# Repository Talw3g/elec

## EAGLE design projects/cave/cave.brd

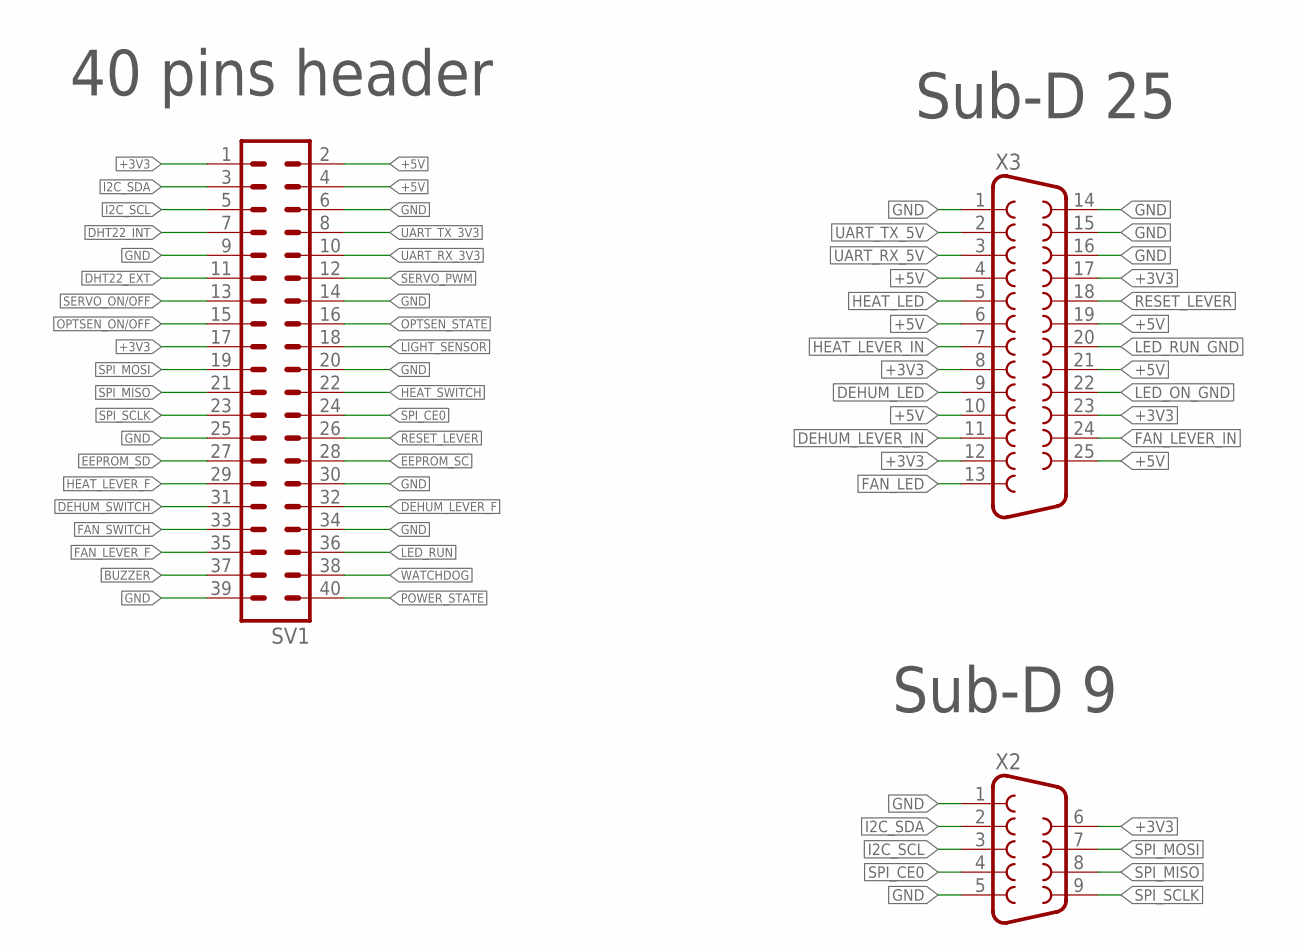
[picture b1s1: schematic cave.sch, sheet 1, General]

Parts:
SV1: MA20-2
X2: F09V
X3: F25V

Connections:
+3V3: SV1.1, SV1.17, X2.6, X3.8, X3.12, X3.17, X3.23; also elsewhere on the board
+5V: SV1.2, SV1.4, X3.4, X3.6, X3.10, X3.19, X3.21, X3.25; also elsewhere on the board
BUZZER: SV1.37; also elsewhere on the board
DEHUM_LED: X3.9; also elsewhere on the board
DEHUM_LEVER_F: SV1.32; also elsewhere on the board
DEHUM_LEVER_IN: X3.11; also elsewhere on the board
DEHUM_SWITCH: SV1.31; also elsewhere on the board
DHT22_EXT: SV1.11; also elsewhere on the board
DHT22_INT: SV1.7; also elsewhere on the board
EEPROM_SC: SV1.28
EEPROM_SD: SV1.27
FAN_LED: X3.13; also elsewhere on the board
FAN_LEVER_F: SV1.35; also elsewhere on the board
FAN_LEVER_IN: X3.24; also elsewhere on the board
FAN_SWITCH: SV1.33; also elsewhere on the board
GND: SV1.6, SV1.9, SV1.14, SV1.20, SV1.25, SV1.30, SV1.34, SV1.39, X2.1, X2.5, X3.1, X3.14, X3.15, X3.16; also elsewhere on the board
HEAT_LED: X3.5; also elsewhere on the board
HEAT_LEVER_F: SV1.29; also elsewhere on the board
HEAT_LEVER_IN: X3.7; also elsewhere on the board
HEAT_SWITCH: SV1.22; also elsewhere on the board
I2C_SCL: SV1.5, X2.3
I2C_SDA: SV1.3, X2.2
LED_ON_GND: X3.22; also elsewhere on the board
LED_RUN: SV1.36; also elsewhere on the board
LED_RUN_GND: X3.20; also elsewhere on the board
LIGHT_SENSOR: SV1.18; also elsewhere on the board
OPTSEN_ON/OFF: SV1.15; also elsewhere on the board
OPTSEN_STATE: SV1.16; also elsewhere on the board
POWER_STATE: SV1.40; also elsewhere on the board
RESET_LEVER: SV1.26, X3.18; also elsewhere on the board
SERVO_ON/OFF: SV1.13; also elsewhere on the board
SERVO_PWM: SV1.12; also elsewhere on the board
SPI_CE0: SV1.24, X2.4
SPI_MISO: SV1.21, X2.8
SPI_MOSI: SV1.19, X2.7
SPI_SCLK: SV1.23, X2.9
UART_RX_3V3: SV1.10; also elsewhere on the board
UART_RX_5V: X3.3; also elsewhere on the board
UART_TX_3V3: SV1.8; also elsewhere on the board
UART_TX_5V: X3.2; also elsewhere on the board
WATCHDOG: SV1.38; also elsewhere on the board

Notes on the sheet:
40 pins header
Sub-D 25
Sub-D 9

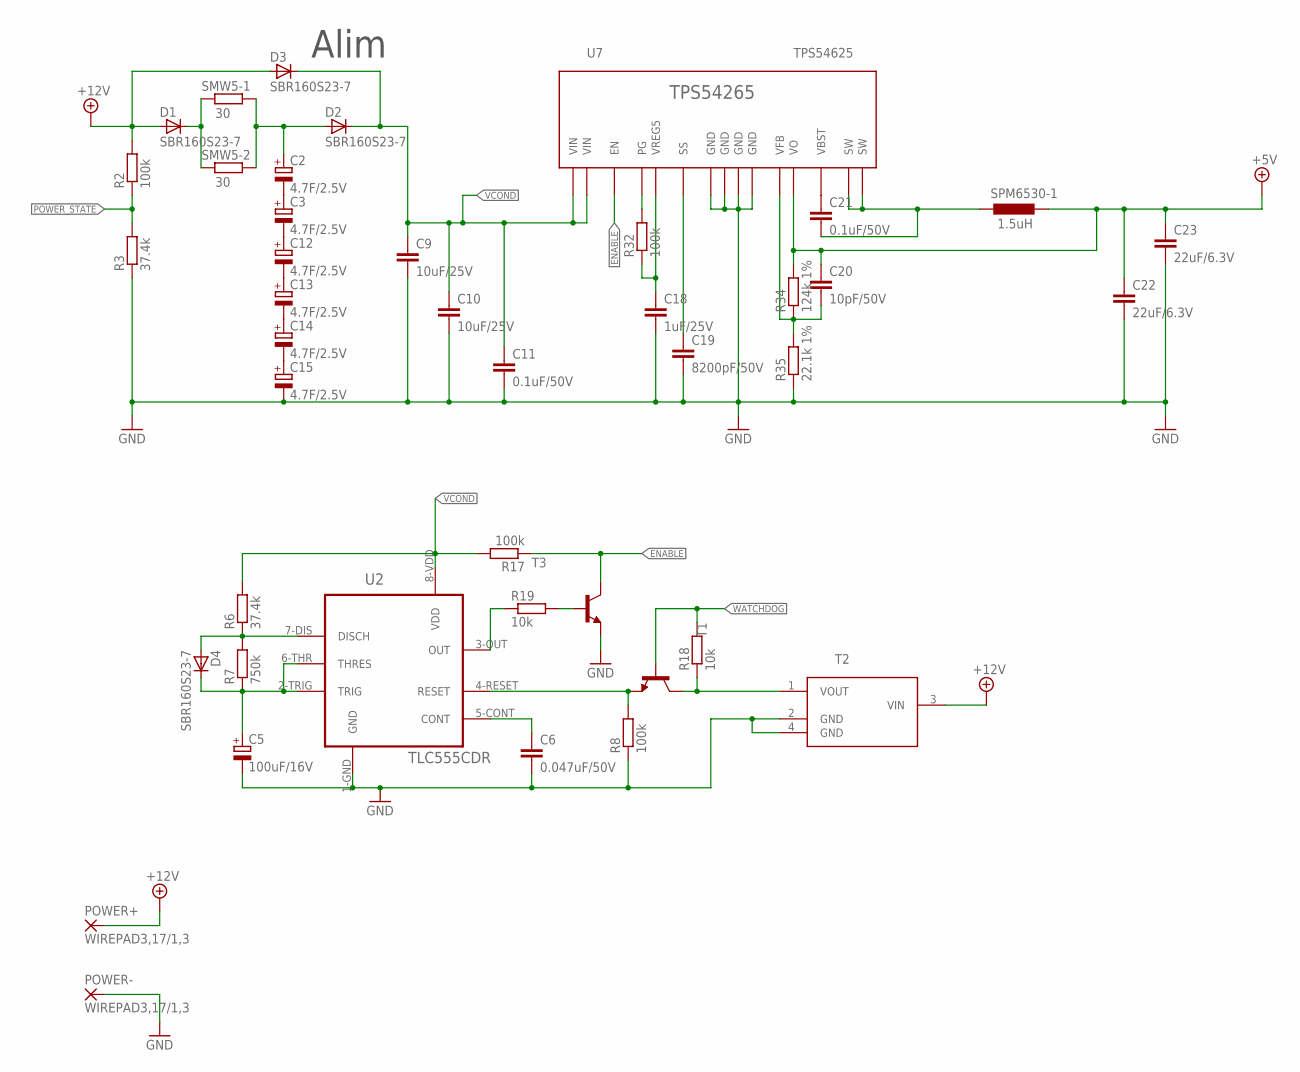
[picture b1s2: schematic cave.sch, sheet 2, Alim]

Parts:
C2, C3, C12, C13, C14, C15: 4.7F/2.5V; E5-10,5
C5: 100uF/16V; D/7343-31W
C6: 0.047uF/50V; C0603
C9, C10: 10uF/25V; C0805
C11, C21: 0.1uF/50V; C0603
C18: 1uF/25V; C0603
C19: 8200pF/50V; C0603
C20: 10pF/50V; C0603
C22, C23: 22uF/6.3V; C0805
D1, D2, D3, D4: SBR160S23-7; SOT23
POWER+: WIREPAD3,17/1,3; 3,17/1,3
POWER-: WIREPAD3,17/1,3; 3,17/1,3
R2, R8, R17, R32: 100k; R0603
R3, R6: 37.4k; R0603
R7: 750k; R0603
R18, R19: 10k; R0603
R34: 124k 1%; R0603
R35: 22.1k 1%; R0603
SMW5-1, SMW5-2: 30; SM_5
SPM6530-1: 1.5uH; 6530
T1, T3: MMBT2369LT1-NPN-SOT23-BEC; SOT23-BEC
T2: L78L33ACUTR; SOT150P400X160-4N
U2: TLC555CDR; SOIC127P600X175-8N
U7: TPS54625; HTSSOP-14

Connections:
+5V: C20.1, C22.1, C23.1, R34.2, SPM6530-1.P$2, U7.P$1 (VO); also elsewhere on the board
+12V: D1.1 (A), D3.1 (A), POWER+.1, R2.2, T2.3 (VIN); also elsewhere on the board
ENABLE: R17.1, T3.C, U7.P$7 (EN)
GND: C5.-, C6.2, C9.2, C10.2, C11.2, C15.-, C18.2, C19.2, C22.2, C23.2, POWER-.1, R3.1, R8.1, R35.1, T2.2 (GND), T2.4 (GND), T3.E, U2.1-GND (GND), U7.P$5 (GND), U7.P$8 (GND), U7.P$9 (GND), U7.P$15 (GND); also elsewhere on the board
unnamed: C2.+, D2.1 (A), SMW5-1.P$2 (2), SMW5-2.P$2 (2)
unnamed: C2.-, C3.+
unnamed: C3.-, C12.+
unnamed: D1.3 (C), SMW5-1.P$1 (1), SMW5-2.P$1 (1)
unnamed: D4.1 (A), R6.1, R7.2, U2.7-DIS (DISCH)
unnamed: C5.+, D4.3 (C), R7.1, U2.2-TRIG (TRIG), U2.6-THR (THRES)
unnamed: C12.-, C13.+
unnamed: C6.1, U2.5-CONT (CONT)
unnamed: R18.1, T1.C, T2.1 (VOUT)
unnamed: R8.2, T1.E, U2.4-RESET (RESET)
unnamed: R19.1, U2.3-OUT (OUT)
unnamed: R19.2, T3.B
unnamed: C13.-, C14.+
unnamed: C14.-, C15.+
unnamed: C18.1, R32.1, U7.P$3 (VREG5)
unnamed: R32.2, U7.P$6 (PG)
unnamed: C19.1, U7.P$4 (SS)
unnamed: C20.2, R34.1, R35.2, U7.P$2 (VFB)
unnamed: C21.1, U7.P$12 (VBST)
unnamed: C21.2, SPM6530-1.P$1, U7.P$10 (SW), U7.P$11 (SW)
POWER_STATE: R2.1, R3.2; also elsewhere on the board
VCOND: C9.1, C10.1, C11.1, D2.3 (C), D3.3 (C), R6.2, R17.2, U2.8-VDD (VDD), U7.P$13 (VIN), U7.P$14 (VIN)
WATCHDOG: R18.2, T1.B; also elsewhere on the board

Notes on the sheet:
Alim

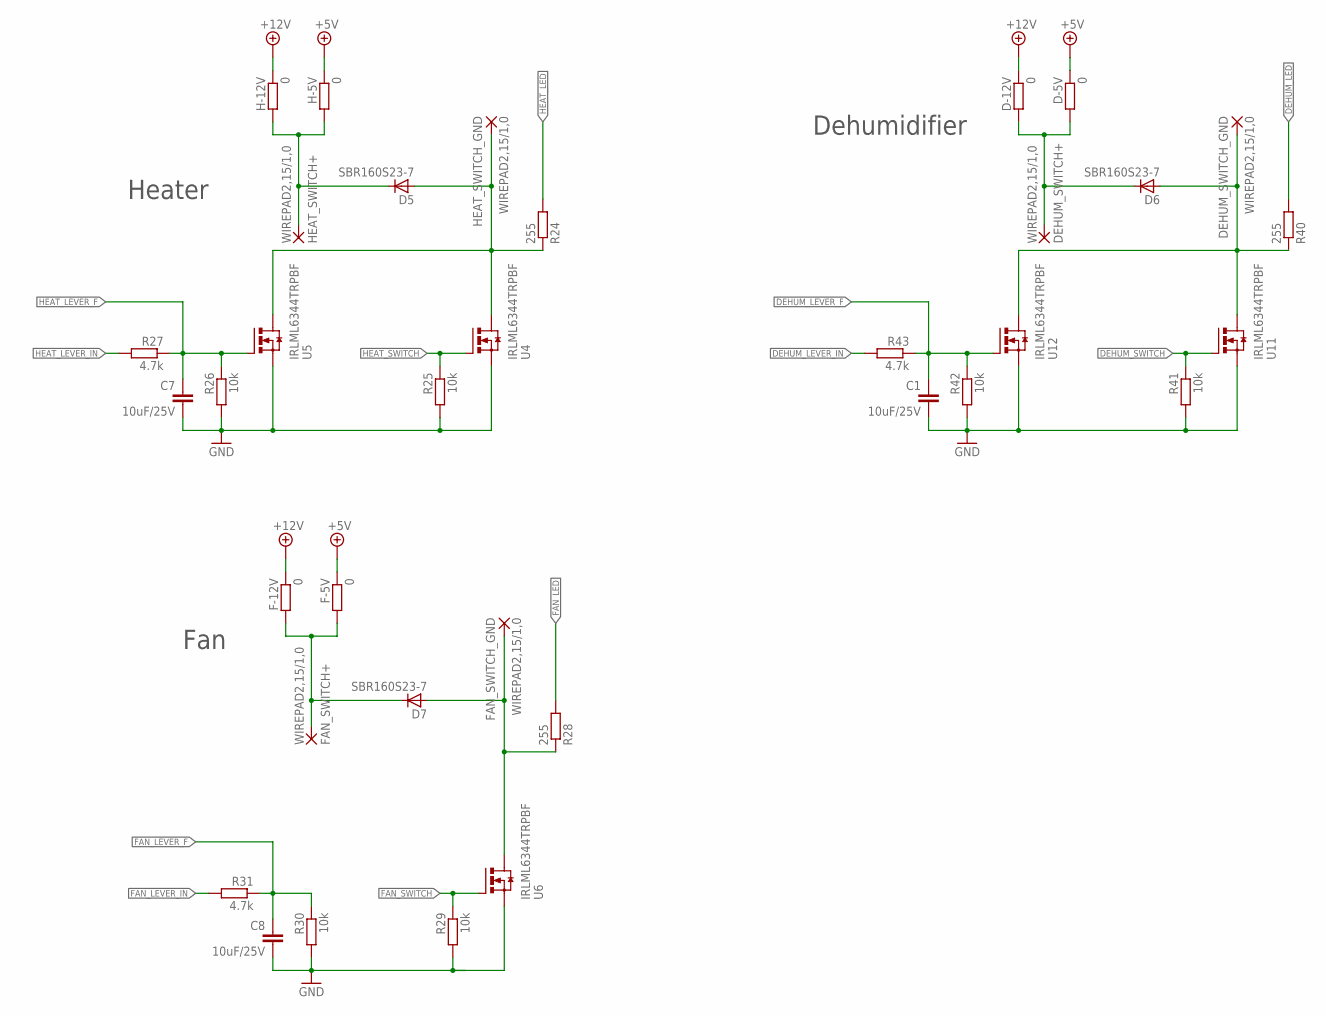
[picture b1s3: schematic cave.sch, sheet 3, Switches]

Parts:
C1, C7, C8: 10uF/25V; C0805
D5, D6, D7: SBR160S23-7; SOT23
D-5V, D-12V: 0; R0805
DEHUM_SWITCH+: WIREPAD2,15/1,0; 2,15/1,0
DEHUM_SWITCH_GND: WIREPAD2,15/1,0; 2,15/1,0
F-5V, F-12V: 0; R0805
FAN_SWITCH+: WIREPAD2,15/1,0; 2,15/1,0
FAN_SWITCH_GND: WIREPAD2,15/1,0; 2,15/1,0
H-5V, H-12V: 0; R0805
HEAT_SWITCH+: WIREPAD2,15/1,0; 2,15/1,0
HEAT_SWITCH_GND: WIREPAD2,15/1,0; 2,15/1,0
R24, R28, R40: 255; R0805
R25, R26, R29, R30, R41, R42: 10k; R0603
R27, R31, R43: 4.7k; R0603
U4, U5, U6, U11, U12: IRLML6344TRPBF; SOT95P240X112-3N

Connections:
+5V: D-5V.1, F-5V.1, H-5V.1; also elsewhere on the board
+12V: D-12V.1, F-12V.1, H-12V.1; also elsewhere on the board
DEHUM_GND: D6.1 (A), DEHUM_SWITCH_GND.1, R40.1, U11.3 (D), U12.3 (D)
DEHUM_LED: R40.2; also elsewhere on the board
DEHUM_LEVER_F: C1.1, R42.1, R43.1, U12.1 (G); also elsewhere on the board
DEHUM_LEVER_IN: R43.2; also elsewhere on the board
DEHUM_SWITCH: R41.1, U11.1 (G); also elsewhere on the board
FAN_GND: D7.1 (A), FAN_SWITCH_GND.1, R28.1, U6.3 (D)
FAN_LED: R28.2; also elsewhere on the board
FAN_LEVER_F: C8.1, R30.1, R31.1; also elsewhere on the board
FAN_LEVER_IN: R31.2; also elsewhere on the board
FAN_SWITCH: R29.1, U6.1 (G); also elsewhere on the board
GND: C1.2, C7.2, C8.2, R25.2, R26.2, R29.2, R30.2, R41.2, R42.2, U4.2 (S), U5.2 (S), U6.2 (S), U11.2 (S), U12.2 (S); also elsewhere on the board
HEAT_GND: D5.1 (A), HEAT_SWITCH_GND.1, R24.1, U4.3 (D), U5.3 (D)
HEAT_LED: R24.2; also elsewhere on the board
HEAT_LEVER_F: C7.1, R26.1, R27.1, U5.1 (G); also elsewhere on the board
HEAT_LEVER_IN: R27.2; also elsewhere on the board
HEAT_SWITCH: R25.1, U4.1 (G); also elsewhere on the board
unnamed: D7.3 (C), F-5V.2, F-12V.2, FAN_SWITCH+.1
unnamed: D5.3 (C), H-5V.2, H-12V.2, HEAT_SWITCH+.1
unnamed: D6.3 (C), D-5V.2, D-12V.2, DEHUM_SWITCH+.1

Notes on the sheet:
Heater
Dehumidifier
Fan

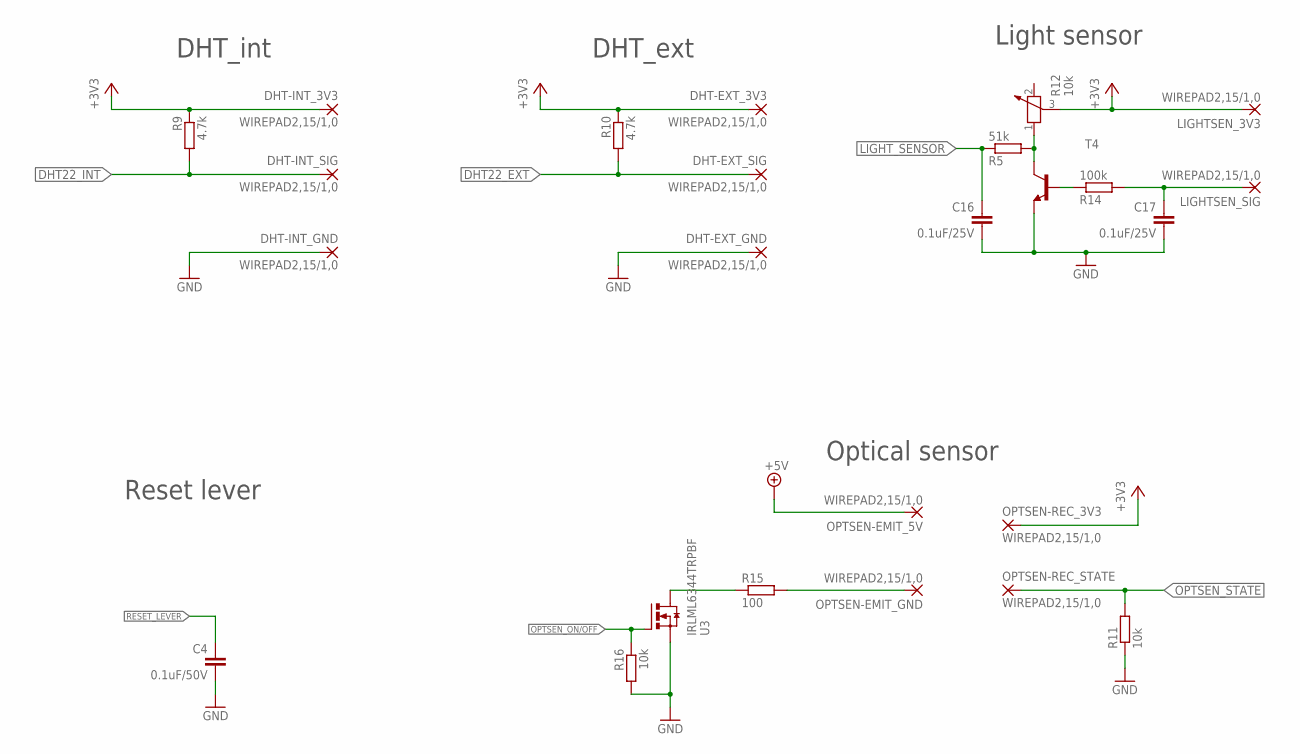
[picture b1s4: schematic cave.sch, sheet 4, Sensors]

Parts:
C4: 0.1uF/50V; C0603
C16, C17: 0.1uF/25V; C0603
DHT-EXT_3V3: WIREPAD2,15/1,0; 2,15/1,0
DHT-EXT_GND: WIREPAD2,15/1,0; 2,15/1,0
DHT-EXT_SIG: WIREPAD2,15/1,0; 2,15/1,0
DHT-INT_3V3: WIREPAD2,15/1,0; 2,15/1,0
DHT-INT_GND: WIREPAD2,15/1,0; 2,15/1,0
DHT-INT_SIG: WIREPAD2,15/1,0; 2,15/1,0
LIGHTSEN_3V3: WIREPAD2,15/1,0; 2,15/1,0
LIGHTSEN_SIG: WIREPAD2,15/1,0; 2,15/1,0
OPTSEN-EMIT_5V: WIREPAD2,15/1,0; 2,15/1,0
OPTSEN-EMIT_GND: WIREPAD2,15/1,0; 2,15/1,0
OPTSEN-REC_3V3: WIREPAD2,15/1,0; 2,15/1,0
OPTSEN-REC_STATE: WIREPAD2,15/1,0; 2,15/1,0
R5: 51k; R0603
R9, R10: 4.7k; R0603
R11, R16: 10k; R0603
R12: 10k; PT-SPIN
R14: 100k; R0603
R15: 100; R0805
T4: MMBT2369LT1-NPN-SOT23-BEC; SOT23-BEC
U3: IRLML6344TRPBF; SOT95P240X112-3N

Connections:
+3V3: DHT-EXT_3V3.1, DHT-INT_3V3.1, LIGHTSEN_3V3.1, OPTSEN-REC_3V3.1, R9.1, R10.1, R12.3; also elsewhere on the board
+5V: OPTSEN-EMIT_5V.1; also elsewhere on the board
DHT22_EXT: DHT-EXT_SIG.1, R10.2; also elsewhere on the board
DHT22_INT: DHT-INT_SIG.1, R9.2; also elsewhere on the board
GND: C4.2, C16.2, C17.2, DHT-EXT_GND.1, DHT-INT_GND.1, R11.1, R16.2, T4.E, U3.2 (S); also elsewhere on the board
LIGHT_SENSOR: C16.1, R5.1; also elsewhere on the board
LIGHT_SENSOR_UNFILTERED: R5.2, R12.1, T4.C
unnamed: OPTSEN-EMIT_GND.1, R15.2
unnamed: R15.1, U3.3 (D)
unnamed: R14.1, T4.B
unnamed: C17.1, LIGHTSEN_SIG.1, R14.2
OPTSEN_ON/OFF: R16.1, U3.1 (G); also elsewhere on the board
OPTSEN_STATE: OPTSEN-REC_STATE.1, R11.2; also elsewhere on the board
RESET_LEVER: C4.1; also elsewhere on the board

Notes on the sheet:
DHT_int
DHT_ext
Optical sensor
Light sensor
Reset lever

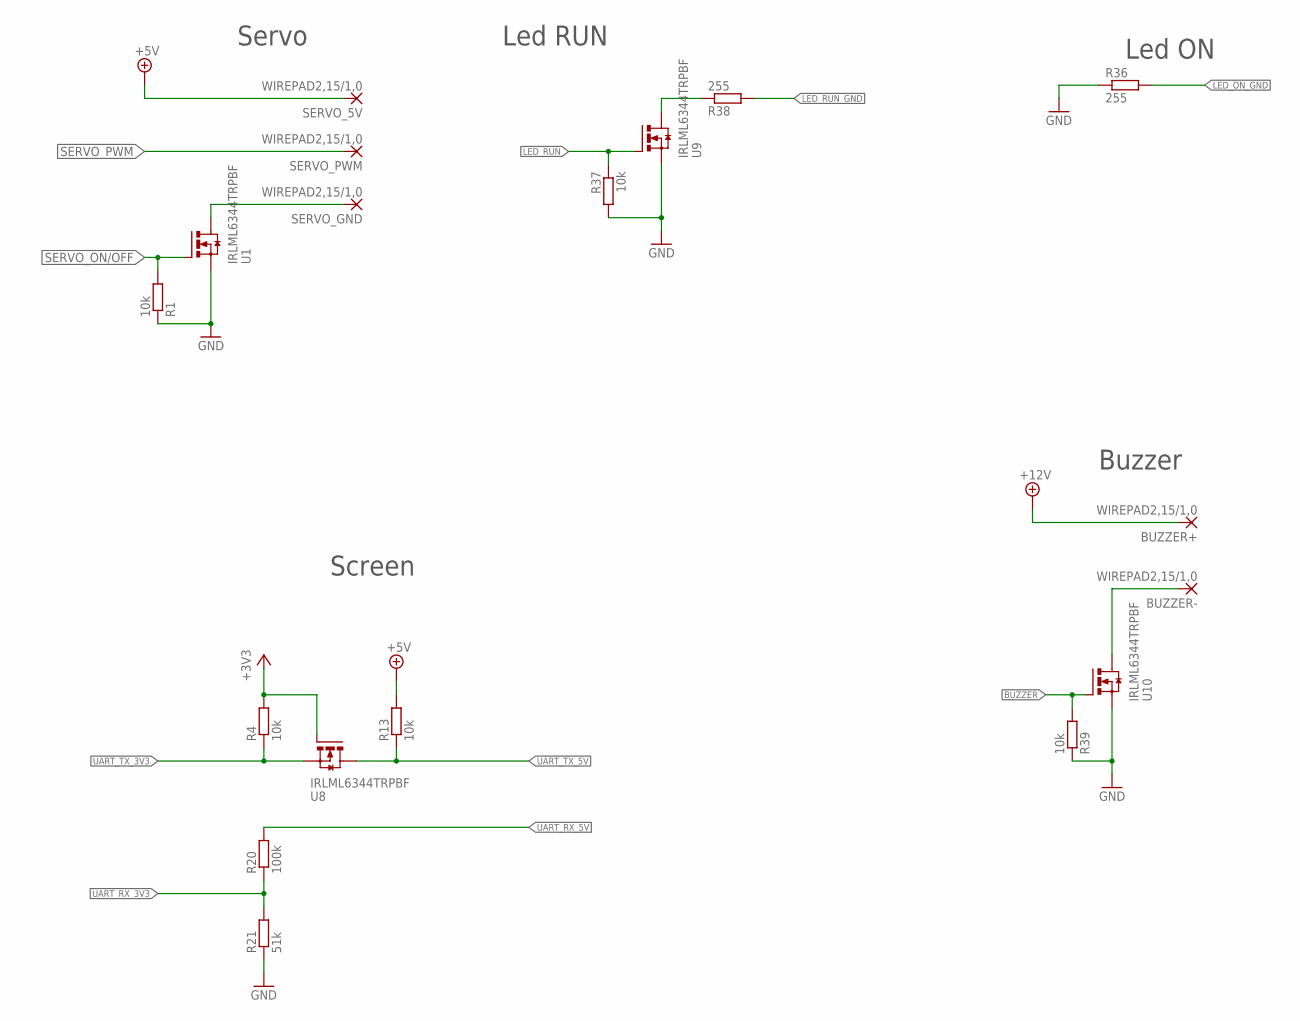
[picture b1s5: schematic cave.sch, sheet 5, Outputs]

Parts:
BUZZER+: WIREPAD2,15/1,0; 2,15/1,0
BUZZER-: WIREPAD2,15/1,0; 2,15/1,0
R1, R4, R13, R37, R39: 10k; R0603
R20: 100k; R0603
R21: 51k; R0603
R36, R38: 255; R0805
SERVO_5V: WIREPAD2,15/1,0; 2,15/1,0
SERVO_GND: WIREPAD2,15/1,0; 2,15/1,0
SERVO_PWM: WIREPAD2,15/1,0; 2,15/1,0
U1, U8, U9, U10: IRLML6344TRPBF; SOT95P240X112-3N

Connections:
+3V3: R4.2, U8.1 (G); also elsewhere on the board
+5V: R13.2, SERVO_5V.1; also elsewhere on the board
+12V: BUZZER+.1; also elsewhere on the board
BUZZER: R39.2, U10.1 (G); also elsewhere on the board
GND: R1.1, R21.1, R36.1, R37.2, R39.1, U1.2 (S), U9.2 (S), U10.2 (S); also elsewhere on the board
LED_ON_GND: R36.2; also elsewhere on the board
LED_RUN: R37.1, U9.1 (G); also elsewhere on the board
LED_RUN_GND: R38.2; also elsewhere on the board
unnamed: SERVO_GND.1, U1.3 (D)
unnamed: BUZZER-.1, U10.3 (D)
unnamed: R38.1, U9.3 (D)
SERVO_ON/OFF: R1.2, U1.1 (G); also elsewhere on the board
SERVO_PWM: SERVO_PWM.1; also elsewhere on the board
UART_RX_3V3: R20.1, R21.2; also elsewhere on the board
UART_RX_5V: R20.2; also elsewhere on the board
UART_TX_3V3: R4.1, U8.2 (S); also elsewhere on the board
UART_TX_5V: R13.1, U8.3 (D); also elsewhere on the board

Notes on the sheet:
Servo
Screen
Led ON
Led RUN
Buzzer

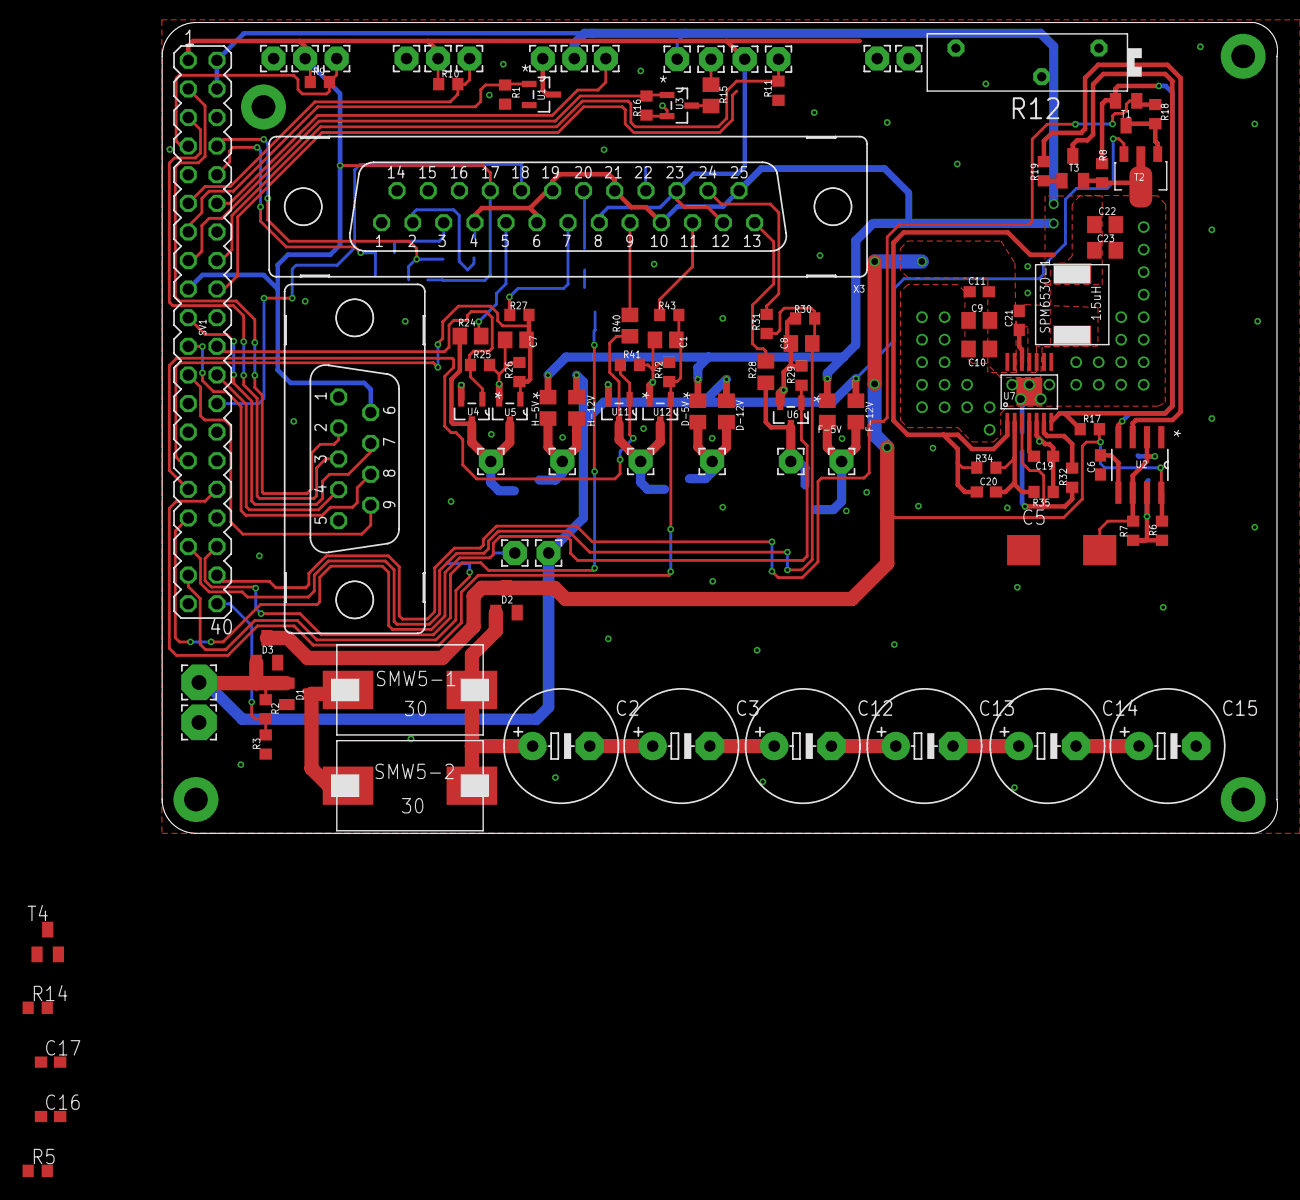
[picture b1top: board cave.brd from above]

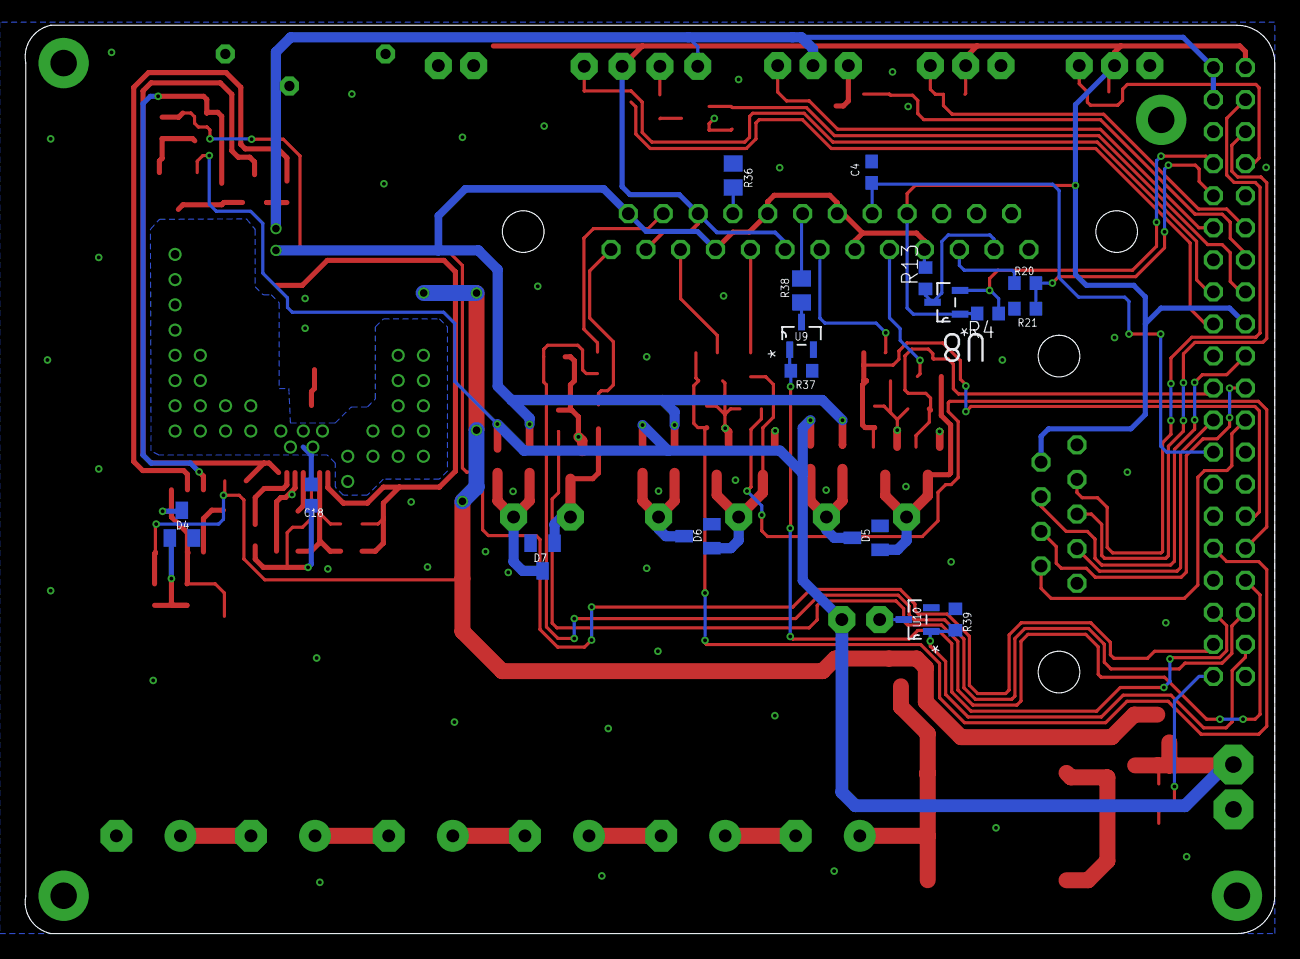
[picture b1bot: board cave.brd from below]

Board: 2 copper layers, 99.0 x 72.0 mm, 123 parts (17 on the bottom side), 76 nets.

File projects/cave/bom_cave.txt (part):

Partlist exported from C:/Users/SOLIDWORKS-FNS/Documents/elec_perso/projects/cave/cave.sch at 27/10/2016 14:40

Qty Value           Device                    Package            Parts                                                                                                                                                                                                                                                                                                                                   Description                                                                                                          MF MPN            OC_FARNELL OC_NEWARK PACKAGE  RATEDVOLTAGE SUPPLIER                TOLERANCE  VALUE
1                   F09V                      F09V               X2                                                                                                                                                                                                                                                                                                                                      SUB-D                                                                                                                                  unknown    unknown                                                                 
1                   F25V                      F25V               X3                                                                                                                                                                                                                                                                                                                                      SUB-D                                                                                                                                  unknown    unknown                                                                 
1                   L78L33ACUTR               SOT150P400X160-4N  T2                                                                                                                                                                                                                                                                                                                                      Positive voltage regulators(Output current up to 100 mA and Output voltages of 3.3; 5; 6; 8; 9; 10; 12; 15; 18;24 V)    L78L33ACUTR    2253467    89K1361   SOT-89                STMicroelectronics                      
1                   MA20-2                    MA20-2             SV1                                                                                                                                                                                                                                                                                                                                     PIN HEADER                                                                                                                             unknown    unknown                                                                 
3                   MMBT2369LT1-NPN-SOT23-BEC SOT23-BEC          T1, T3, T4                                                                                                                                                                                                                                                                                                                              NPN Transistror                                                                                                                                                                                                           
6   0               R-EU_R0805                R0805              D-5V, D-12V, F-5V, F-12V, H-5V, H-12V                                                                                                                                                                                                                                                                                                   RESISTOR, European symbol                                                                                                                                                                                                 
1   0.047uF/50V     C-EUC0603                 C0603              C6                                                                                                                                                                                                                                                                                                                                      CAPACITOR, European symbol                                                                                                                                                                                                
2   0.1uF/50V       C-EUC0603                 C0603              C11, C21                                                                                                                                                                                                                                                                                                                                CAPACITOR, European symbol                                                                                                                                                                                                
3   0.47F           EECF5R5U474-D21.5         CAP_EECF5          C2, C3, C12                                                                                                                                                                                                                                                                                                                             Electric Double Layer Capacitors                                                                                        EECF5R5U474    9692711    96K9365             5.5V        PANASONIC               -20%, +80% 0.47F
1   1.5uH           SPM6530                   6530               SPM6530-1                                                                                                                                                                                                                                                                                                                                                                                                                                                                                                                                                         
1   100             R-EU_R0805                R0805              R15                                                                                                                                                                                                                                                                                                                                     RESISTOR, European symbol                                                                                                                                                                                                 
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
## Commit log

2016-10-13 5V step down regulator routed
2016-10-14 finished routing 5V step down regulator
2016-10-14 555 components placed but not routed. Updated 555 pin description in package.
2016-10-14 wip on routing
2016-10-16 "power" layout makeover in progress
2016-10-16 trying to tidy up the power sector of the board
2016-10-16 HEAT sector routed, but not linked to the rest of the board.
2016-10-16 "switches" sector routed but not linked to the rest of the board.
2016-10-17 "power" sector modification in progress.
2016-10-17 WIP on "power" sector
2016-10-17 WIP on "sensor" sector
2016-10-18 All components layed out, but routing still to be done.
2016-10-19 Component layout in progress.
2016-10-20 Routing IO wirepads to 40-pin header.
2016-10-20 Routing in progress...
2016-10-20 Routing in progress... Added "Routing_prefs" script in lib folder to set custom default values and shortcuts. To run it, add "eagle_libs" folder as a script directory in eagle, and add "SCRIPT Routin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
2016-10-21 Signal routing done (?), power still to be routed.
2016-10-21 Routing done !! Changed 5V to +5V on 25-pin Sub-D. Modified Routing_prefs script.
2016-10-21 Added fixing holes for M2 screws (2.2mm vias). Rounded corners.
2016-10-22 Added silkscreen on board (_tsilk layer). Changed GND pin name in STM library (moved to personnal lib).
2016-10-24 Silkscreen moved to tDocu layer. Added some space between the MOSFET. Modified 40-pin-header package's silkscreen and saved it to HE_254.lbr.
2016-10-25 Changed 250ohm-0603 led res to 255ohm-0805. Generated BOM
2016-10-26 Updated BOM regarding order status.
2016-10-27 Reset lever circuit added to schematic and board ! BOM updated.
2016-10-27 Corrected last commit's error on BOM
2016-11-03 Changed 5V regulator's package to be more solderable, updated board accordingly.
2016-11-03 Changed to Seeed's DRU -> min drill changed to 12mil (updated all vias)
2016-11-03 Added Seeed's DRU file and Taz logo in B&W
2016-11-03 Board dimension reduced to 99x70mm (Seeed's limitations). Gerber revA generated
2016-11-04 Changed wirepads positioning to keep the "GND-POW-SIG" pattern. Done some rerouting. tnames layer has to be clarified to be printed in the silkscreen.
2016-11-05 _tsilk moved to tDocu layer. tnames rearranged, silkscreen OK.
2016-11-05 Added slide_switch lib.
2016-11-07 Added free wheel diode between the relays' terminal.
2016-11-08 RevA : gerber done and into production. Added a cleaner script to delete eagle's backup files.
2016-11-10 Fixed silkscreen error on top-board wirepads (forgot to update it after a81e98b). Changed some ill-named-nets' names for relays' GND.
2016-12-14 MAJOR MODIFICATIONS: Changed power capacitor : previous ones didn't sustain discharge current Changed 555 capacitor : previous one was at 6.3V max (instead of 12V), AND not accurate enough -> switch 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
2016-12-14 DHT22 circuit : the 4.7kOhm resistor change to pullup instead of pulldown (pulldown NOT working). Now DHT22 readings work fine.
2016-12-16 UART TX level shifter was NOT working, updated schematic and board.
2016-12-16 Modified light_sensor schematic to improve sensibility, routing to be done (wrong package for potentiometer).
2016-12-18 GPIO for reset_lever is pulled up on the RPi, so we need to pull it down...
2016-12-19 Reset lever is now connected to GND instead of 3V3, and ouputs directly to RPi (with a 100nF capa between reset_lever and GND)
2018-07-17 Added RC filter to light sensor (not routed).
